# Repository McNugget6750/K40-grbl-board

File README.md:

_**K40-grbl-board**_

A PCB layout and schematic.

Made with Eagle PCB 7.4.0 Light

This board comes from here: https://github.com/McNugget6750/K40-grbl-board
Author: Timo Birnschein (timo.birnschein at microforge.de)
Please consider giving credit where credit is due.
Please check for updates in the future.

Based on schematics from https://github.com/txjammer (seems offline)

_**DISCLAMER!**_

USE AT YOU OWN RISK!
I CANNOT BE MADE RESPONSIBLE FOR ANY PROBLEMS THAT MIGHT OCCUR WHILE USING THIS.
THIS IS A HOBBY DEVELOPMENT AND NO TESTING HAS BEEN DONE TO ENSURE THE SAVETY OF ANY
OF YOUR EQUIPMENT OR YOUR HOUSE, YOUR LIFE OR ANYTHING ELSE! DO NOT USE UNLESS YOU UNDERSTAND
THIS! WORKING WITH LASERS AND HIGH VOLTAGE POWER SUPPLIES IS DANGEROUS AND SHOULD
ONLY BE DONE BY EXPERIENCED PEOPLE! NEVER USE WITHOUT LINE OF SIGHT TO THE MACHINE!!
YOUR LASER WILL EVENTUALLY BE ON FIRE! IT HAPPENED TO EVERYONE OF US BEFORE!
ALWAYS BE CAUTIOUS! ALWAYS WATCH YOUR MACHINE WHILE OPERATING IT!

_**Requirements**_

* an arduino nano w atmega328p loaded with grbl http://github.com/grbl/grbl
* 2 Pololu A4988 Stepper motor drivers with current limit set to ~1A (Vref=0.4V)
* a ribbon connector from the original moshi board or this one: http://www.digikey.com/product-search/en?keywords=A100331-ND
* a four pole power connector: MTA04-156 with this package: 1X4MTA
* 4x1 pin header or one of the original moshi stepper motor driver connectors
* grbl form from here: https://github.com/McNugget6750/grbl

_**Software to control the GRBL Laser for cutting**_

I'm using dxf2gcode (with the configurations and source files included in this repository): https://sourceforge.net/projects/dxf2gcode

I also use GRBL-Controller (with the grbl configuration file included in this repository): http://zapmaker.org/projects/grbl-controller-3-0/

My grbl works with relative coordinates. Please keep that in mind.

_**GRBL Config Modifications**_
Modifications for config.h are required!

Modify homing cycle:
- #define HOMING_CYCLE_0 (1<<X_AXIS)
- #define HOMING_CYCLE_1 (1<<Y_AXIS)

Invert spindle enable pin by enabling:
- #define INVERT_SPINDLE_ENABLE_PIN // Default disabled. Uncomment to enable.

Enable variable spindle speed if not done by default. This gives you hardware PWM on Pin D11.
- #define VARIABLE_SPINDLE // Default enabled. Comment to disable.

Remap spindle enable pin to pin D13 by enabling (WARNING! WILL BE PULLED LOW BY BOOT LOADER DURING POWER UP! DEACTIVATE YOUR LASER DURING STARTUP OF BOARD IN ORDER TO PREVENT FULL POWER BURNS AT STARTUP.):
- #define USE_SPINDLE_DIR_AS_ENABLE_PIN // Default disabled. Uncomment to enable.

In file spindle_control.c I changed the PWM prescaler for the laser to make it more precise and easier to control by changing line 94 from
- TCCRB_REGISTER = (TCCRB_REGISTER & 0b11111000) | 0x02; // set to 1/8 Prescaler
to
- TCCRB_REGISTER = (TCCRB_REGISTER & 0b11111000) | 0x01; // set to No Prescaling

_**GRBL Configuration that currently sort of works**_
```
$0=10 (step pulse, usec)
$1=25 (step idle delay, msec)
$2=0 (step port invert mask:00000000)
$3=1 (dir port invert mask:00000001)
$4=0 (step enable invert, bool)
$5=1 (limit pins invert, bool)
$6=0 (probe pin invert, bool)
$10=3 (status report mask:00000011)
$11=0.010 (junction deviation, mm)
$12=0.002 (arc tolerance, mm)
$13=0 (report inches, bool)
$20=0 (soft limits, bool)
$21=0 (hard limits, bool)
$22=1 (homing cycle, bool)
$23=3 (homing dir invert mask:00000011)
$24=200.000 (homing feed, mm/min)
$25=8000.000 (homing seek, mm/min)
$26=250 (homing debounce, msec)
$27=1.000 (homing pull-off, mm)
$100=157.575 (x, step/mm)
$101=157.575 (y, step/mm)
$102=250.000 (z, step/mm)
$110=12000.000 (x max rate, mm/min)
$111=12000.000 (y max rate, mm/min)
$112=12000.000 (z max rate, mm/min)
$120=4000.000 (x accel, mm/sec^2)
$121=4000.000 (y accel, mm/sec^2)
$122=1000.000 (z accel, mm/sec^2)
$130=200.000 (x max travel, mm)
$131=300.000 (y max travel, mm)
$132=10.000 (z max travel, mm)
```

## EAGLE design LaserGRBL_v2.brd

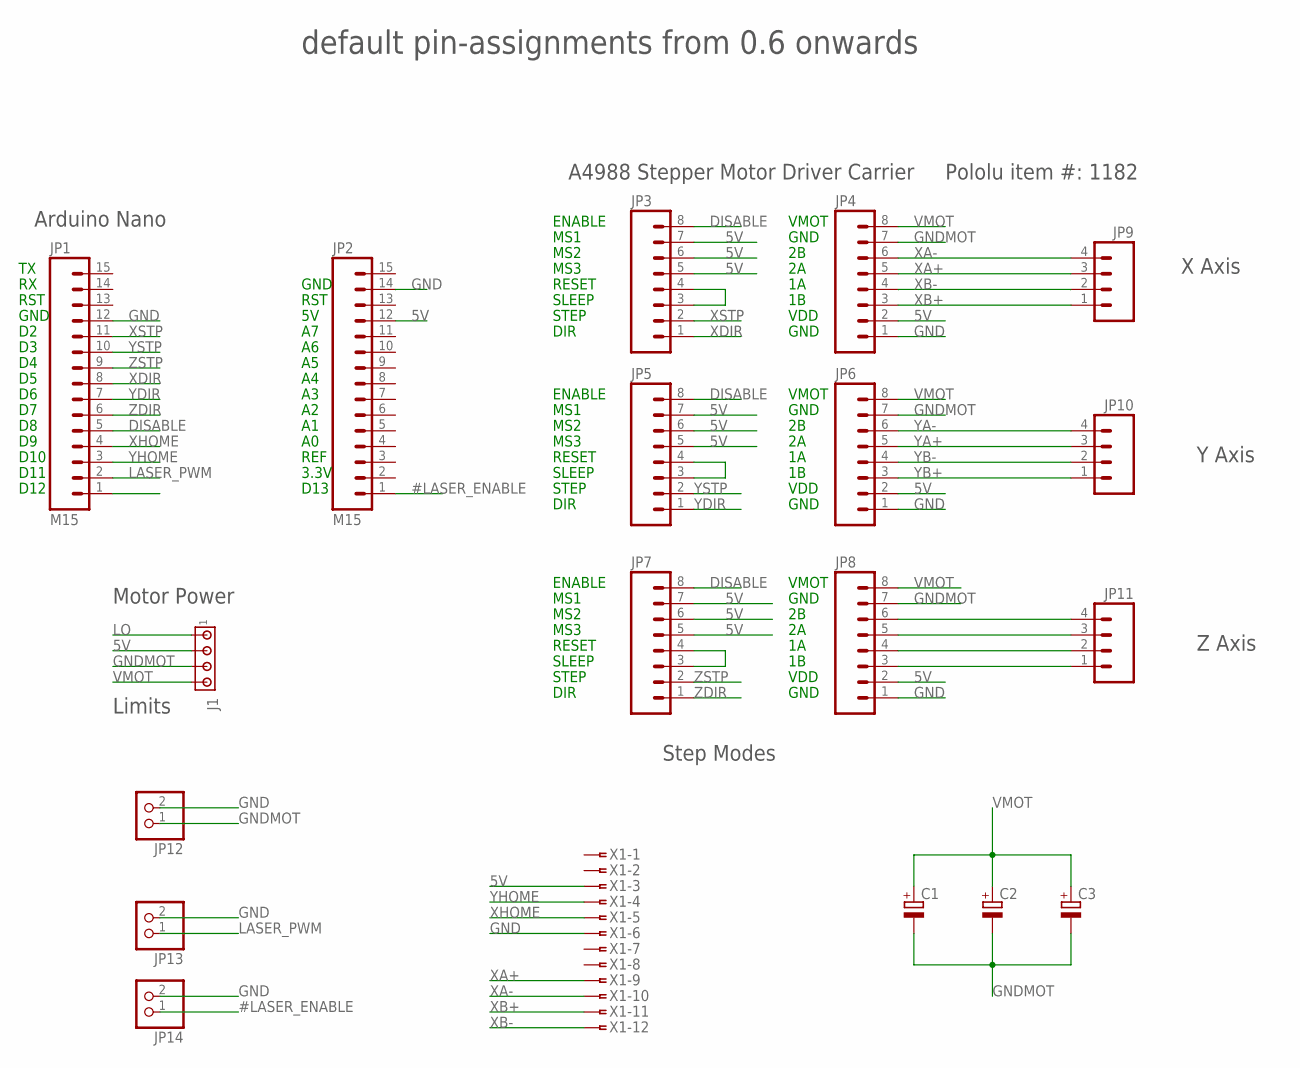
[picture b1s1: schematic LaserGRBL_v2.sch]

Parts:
C1, C2, C3: CPOL-EUE5-10.5; E5-10,5
J1: MTA04-156; 1X4MTA
JP1, JP2: M15; 1X15
JP3, JP4, JP5, JP6, JP7, JP8: M08LONGPADS; 1X08_LONGPADS
JP9, JP10, JP11: M04LONGPADS; 1X04_LONGPADS
JP12, JP13, JP14: PINHD-1X2; 1X02
X1: FSIDE-12

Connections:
5V: J1.2, JP2.12, JP3.5, JP3.6, JP3.7, JP4.2, JP5.5, JP5.6, JP5.7, JP6.2, JP7.5, JP7.6, JP7.7, JP8.2, X1.3
#LASER_ENABLE: JP2.1, JP14.1
DISABLE: JP1.5, JP3.8, JP5.8, JP7.8
GND: JP1.12, JP2.14, JP4.1, JP6.1, JP8.1, JP12.2, JP13.2, JP14.2, X1.6
GNDMOT: C1.-, C2.-, C3.-, J1.3, JP4.7, JP6.7, JP8.7, JP12.1
LASER_PWM: JP1.2, JP13.1
LO: J1.1
unnamed: JP5.3, JP5.4
unnamed: JP8.6, JP11.4
unnamed: JP8.5, JP11.3
unnamed: JP8.4, JP11.2
unnamed: JP8.3, JP11.1
unnamed: JP7.3, JP7.4
unnamed: JP3.3, JP3.4
VMOT: C1.+, C2.+, C3.+, J1.4, JP4.8, JP6.8, JP8.8
XA+: JP4.5, JP9.3, X1.9
XA-: JP4.6, JP9.4, X1.10
XB+: JP4.3, JP9.1, X1.11
XB-: JP4.4, JP9.2, X1.12
XDIR: JP1.8, JP3.1
XHOME: JP1.4, X1.5
XSTP: JP1.11, JP3.2
YA+: JP6.5, JP10.3
YA-: JP6.6, JP10.4
YB+: JP6.3, JP10.1
YB-: JP6.4, JP10.2
YDIR: JP1.7, JP5.1
YHOME: JP1.3, X1.4
YSTP: JP1.10, JP5.2
ZDIR: JP1.6, JP7.1
ZSTP: JP1.9, JP7.2

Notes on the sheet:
D10
GND
D11
D12
DIR
STEP
SLEEP
MS3
MS2
MS1
ENABLE
RESET
VDD
VMOT
default pin-assignments from 0.6 onwards
Step Modes
Arduino Nano
A4988 Stepper Motor Driver Carrier
Pololu item #: 1182
Motor Power
RST
REF
3.3V
D13
Limits
X Axis
Y Axis
Z Axis

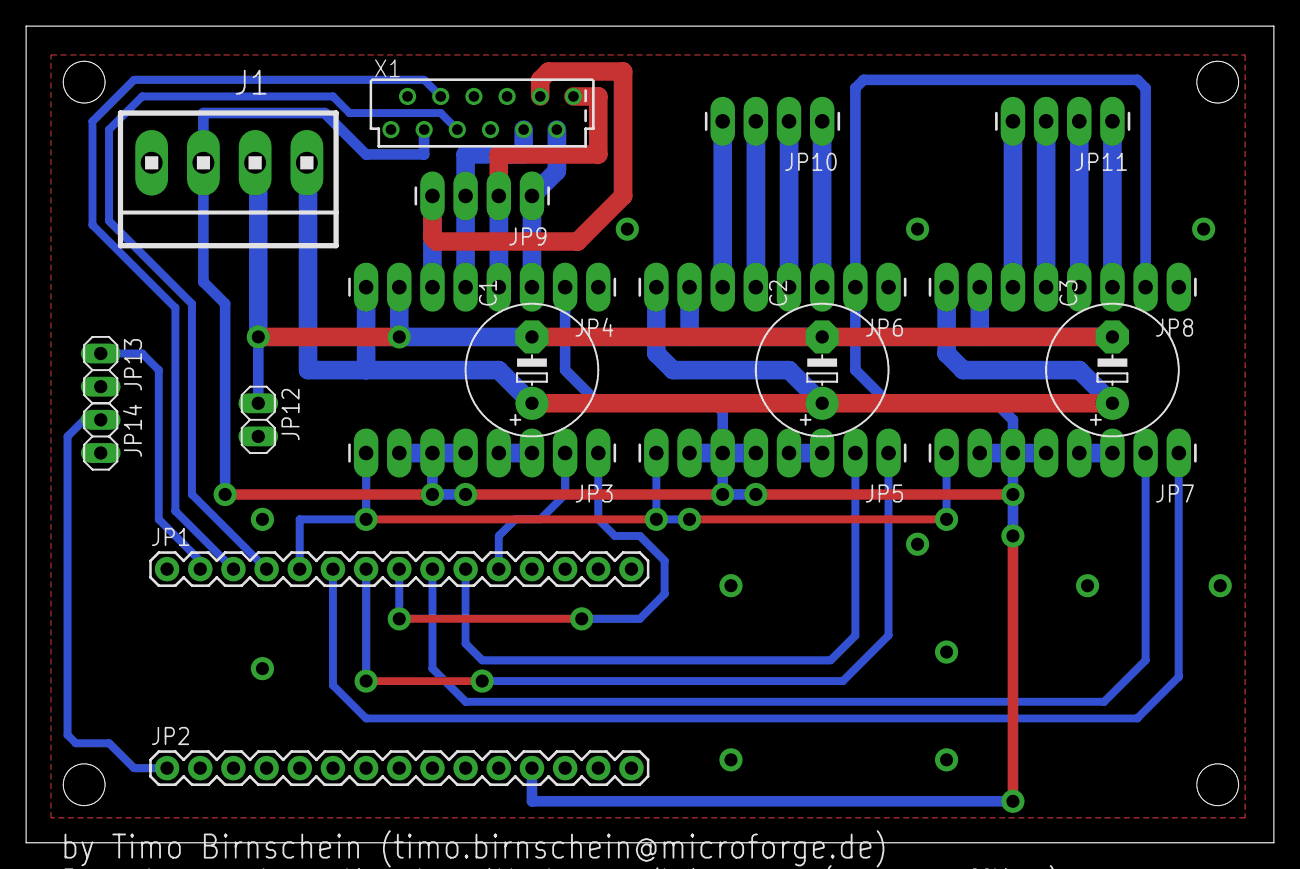
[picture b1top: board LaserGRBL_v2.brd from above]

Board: 2 copper layers, 95.5 x 62.5 mm, 19 parts (0 on the bottom side), 30 nets.

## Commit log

2016-10-05 Version 0.1 of the K40 grbl compatible board.
2016-10-05 Added pictures
2016-10-05 Changed readme
2016-10-06 Some changes to the board file to make it manufacturable.
2016-10-06 Adding a couple of configs and grbl source files that I modified.
2016-10-06 Modified readme with extra software section.
2016-10-07 Adding my current working grbl 0.9j firmware with ported realtime extensions for planned variable laser power from Nick Williams grbl repository. One last thing I don't understand yet: After homing a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
2016-10-07 just a non empty commit
2016-10-07 updated grbl config
2016-10-07 removed grbl from this repository. Now here: https://github.com/McNugget6750/grbl
2016-10-07 changed config to absolute since it is now working fine
